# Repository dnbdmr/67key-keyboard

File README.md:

# A mechanical keyboard with a Thinkpad Trackpoint module installed

- Uses a trackpoint module from an old laptop keyboard. Some more details in hw/
- Uses Microchip SAMD21 MCU with TinyUSB
- Shift registers instead of key matrix

[Schematic](media/67keys-trackpoint.pdf)

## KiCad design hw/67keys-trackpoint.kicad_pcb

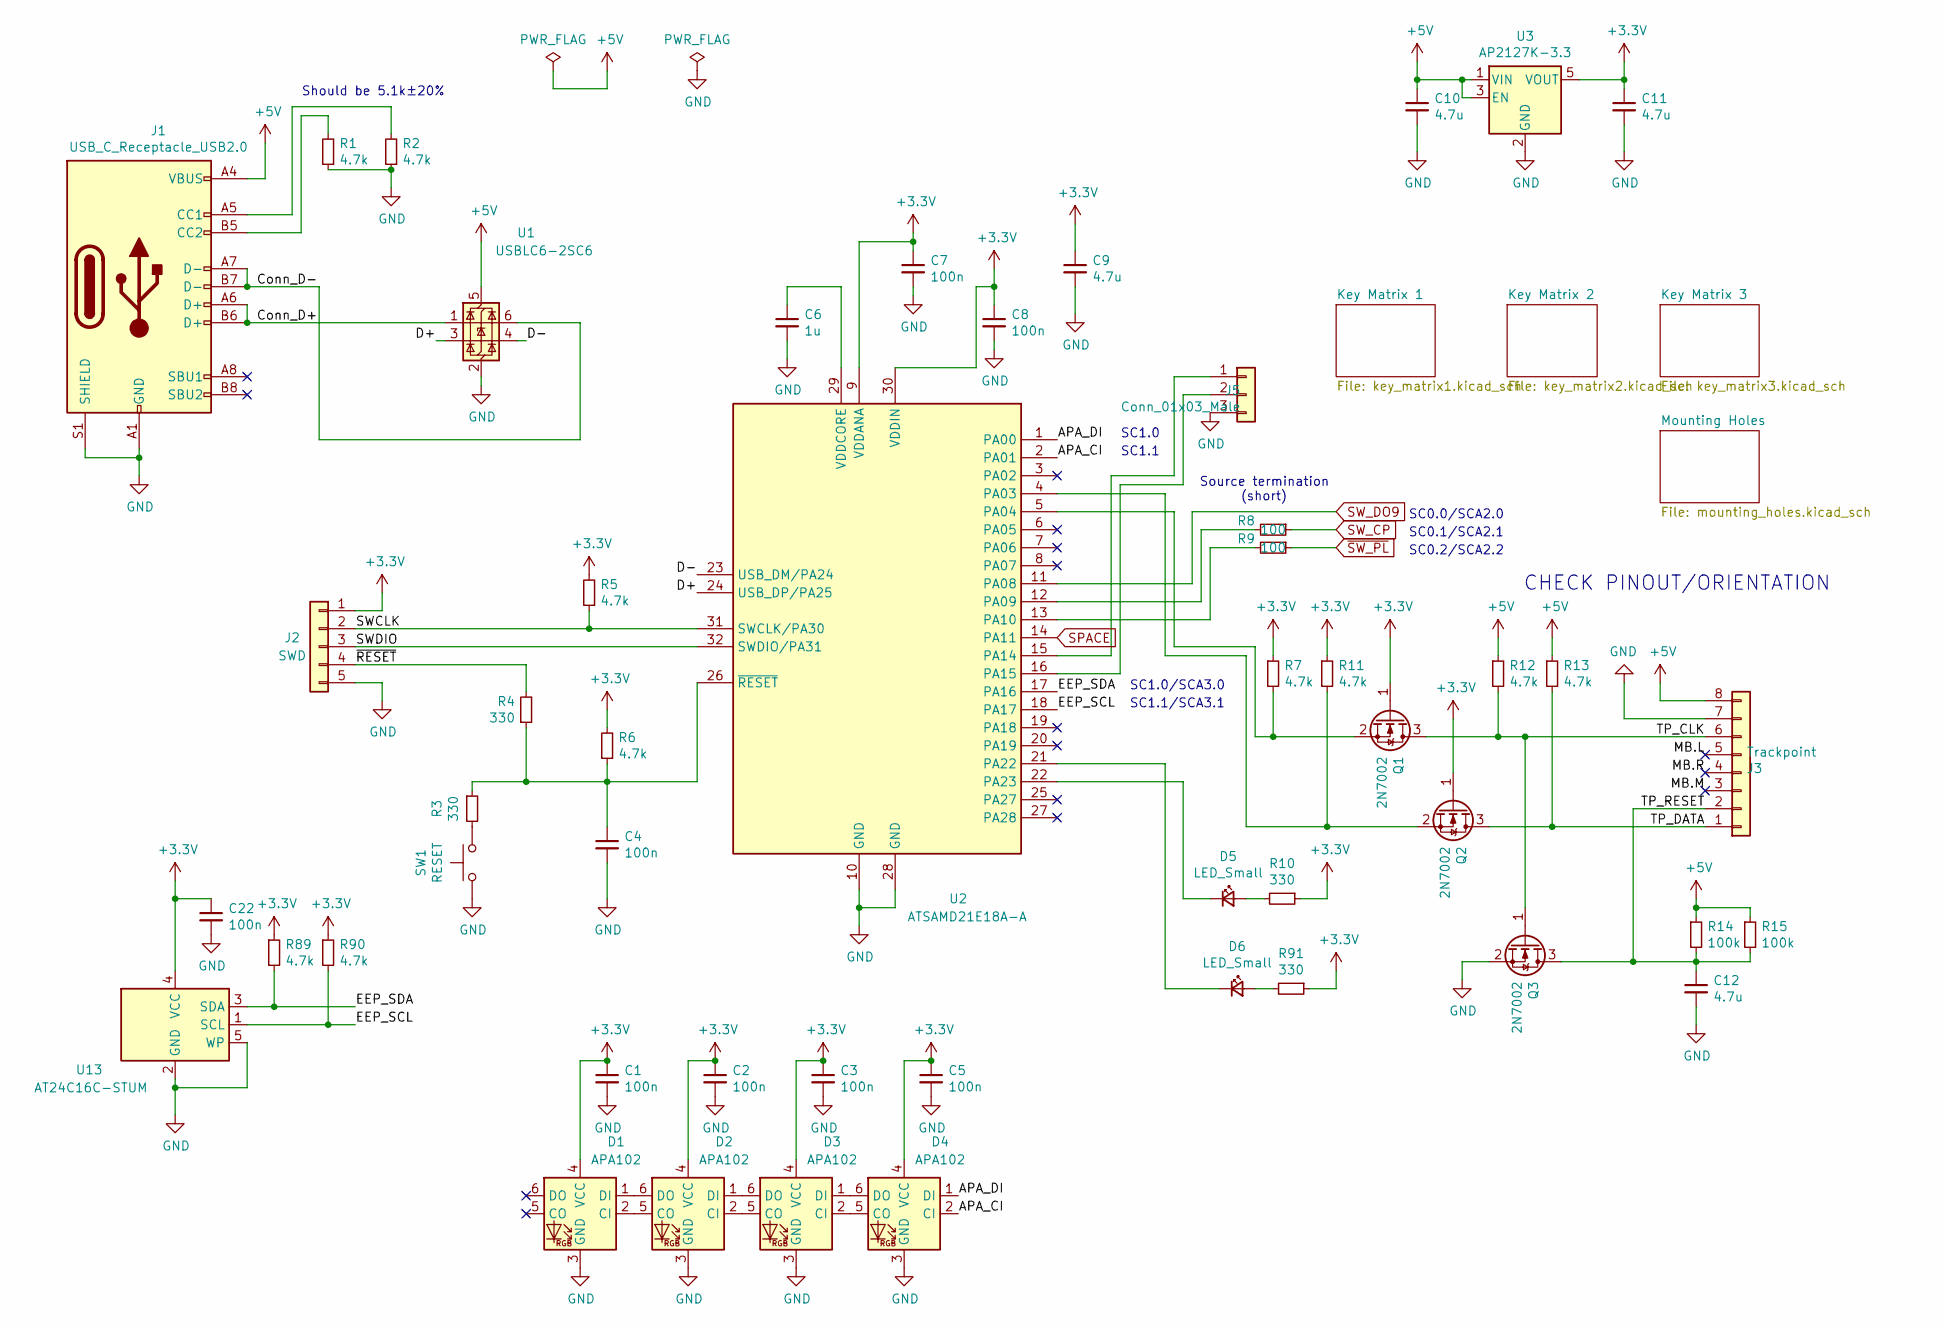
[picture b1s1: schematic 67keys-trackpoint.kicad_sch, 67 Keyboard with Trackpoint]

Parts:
C1, C2, C3, C4, C5, C7, C8, C22: 100n; C_0603_1608Metric_Pad1.08x0.95mm_HandSolder
C6: 1u; C_0603_1608Metric_Pad1.08x0.95mm_HandSolder
C9, C10, C11, C12: 4.7u; C_0603_1608Metric_Pad1.08x0.95mm_HandSolder
D1, D2, D3, D4: APA102; LED_RGB_5050-6
D5, D6: LED_Small; LED_0805_2012Metric_Pad1.15x1.40mm_HandSolder
J1: USB_C_Receptacle_USB2.0; USB_C_Receptacle_GCT_USB4085
J2: SWD; PinHeader_1x05_P2.54mm_Vertical
J3: Trackpoint; TE_84952-8_1x08-1MP_P1.0mm_Horizontal
J5: Conn_01x03_Male; PinHeader_1x03_P2.54mm_Vertical
Q1, Q2, Q3: 2N7002; SOT-23
R1, R2, R5, R6, R7, R11, R12, R13, R89, R90: 4.7k; R_0603_1608Metric_Pad0.98x0.95mm_HandSolder
R3, R4, R10, R91: 330; R_0603_1608Metric_Pad0.98x0.95mm_HandSolder
R8, R9: 100; R_0603_1608Metric_Pad0.98x0.95mm_HandSolder
R14, R15: 100k; R_0603_1608Metric_Pad0.98x0.95mm_HandSolder
SW1: RESET; SW_SPST_TL3305A
U1: USBLC6-2SC6; SOT-23-6
U2: ATSAMD21E18A-A; TQFP-32_7x7mm_P0.8mm
U3: AP2127K-3.3; SOT-23-5
U13: AT24C16C-STUM; SOT-23-5

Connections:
+3V3: C1.1, C2.1, C3.1, C5.1, C7.1, C8.1, C9.1, C11.1, C22.1, D1.4 (VCC), D2.4 (VCC), D3.4 (VCC), D4.4 (VCC), J2.1, Q1.1 (G), Q2.1 (G), R5.2, R6.2, R7.1, R10.1, R11.1, R89.1, R90.1, R91.1, U2.9 (VDDANA), U2.30 (VDDIN), U3.5 (VOUT), U13.4 (VCC); also elsewhere on the board
+5V: C10.1, J1.A4 (VBUS), J1.A9 (VBUS), J1.B4 (VBUS), J1.B9 (VBUS), J3.8, R12.1, R13.1, R14.1, R15.1, U1.5 (VBUS), U3.1 (VIN), U3.3 (EN)
/APA_CI: D4.2 (CI), U2.2 (PA01)
/APA_DI: D4.1 (DI), U2.1 (PA00)
/EEP_SCL: R90.2, U2.18 (PA17), U13.1 (SCL)
/EEP_SDA: R89.2, U2.17 (PA16), U13.3 (SDA)
/SWCLK: J2.2, R5.1, U2.31 (SWCLK/PA30)
/SWDIO: J2.3, U2.32 (SWDIO/PA31)
/TP_CLK: J3.6, Q1.3 (D), Q3.1 (G), R12.2
/TP_DATA: J3.1, Q2.3 (D), R13.2
/TP_RESET: C12.1, J3.2, Q3.3 (D), R14.2, R15.2
/~RESET: J2.4, R4.2
GND: C1.2, C2.2, C3.2, C4.2, C5.2, C6.2, C7.2, C8.2, C9.2, C10.2, C11.2, C12.2, C22.2, D1.3 (GND), D2.3 (GND), D3.3 (GND), D4.3 (GND), J1.A1 (GND), J1.A12 (GND), J1.B1 (GND), J1.B12 (GND), J1.S1 (SHIELD), J2.5, J3.7, J5.3, Q3.2 (S), R1.1, R2.1, SW1.1, U1.2 (GND), U2.10 (GND), U2.28 (GND), U3.2 (GND), U13.2 (GND), U13.5 (WP); also elsewhere on the board
unnamed: C4.1, R3.1, R4.1, R6.1, U2.26 (~RESET)
unnamed: C6.1, U2.29 (VDDCORE)
unnamed: D1.1 (DI), D2.6 (DO)
unnamed: D1.2 (CI), D2.5 (CO)
unnamed: D2.1 (DI), D3.6 (DO)
unnamed: D2.2 (CI), D3.5 (CO)
unnamed: D3.1 (DI), D4.6 (DO)
unnamed: D3.2 (CI), D4.5 (CO)
unnamed: D5.1 (K), U2.22 (PA23)
unnamed: D5.2 (A), R10.2
unnamed: D6.1 (K), U2.21 (PA22)
unnamed: D6.2 (A), R91.2
unnamed: J1.A5 (CC1), R2.2
unnamed: J1.B5 (CC2), R1.2
unnamed: J5.1, U2.15 (PA14)
unnamed: J5.2, U2.16 (PA15)
unnamed: Q1.2 (S), R7.2, U2.5 (PA04)
unnamed: Q2.2 (S), R11.2, U2.4 (PA03)
unnamed: R3.2, SW1.2
unnamed: R8.2, U2.12 (PA09)
unnamed: R9.2, U2.13 (PA10)
SPACE: U2.14 (PA11); also elsewhere on the board
SW_CP: R8.1; also elsewhere on the board
SW_DO9: U2.11 (PA08); also elsewhere on the board
~SW_PL: R9.1; also elsewhere on the board

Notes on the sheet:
SC1.0/SCA3.0
CHECK PINOUT/ORIENTATION
SC1.0
SC1.1
SC0.2/SCA2.2
SC0.0/SCA2.0
SC0.1/SCA2.1
SC1.1/SCA3.1
Should be 5.1k±20%
Source termination (short)

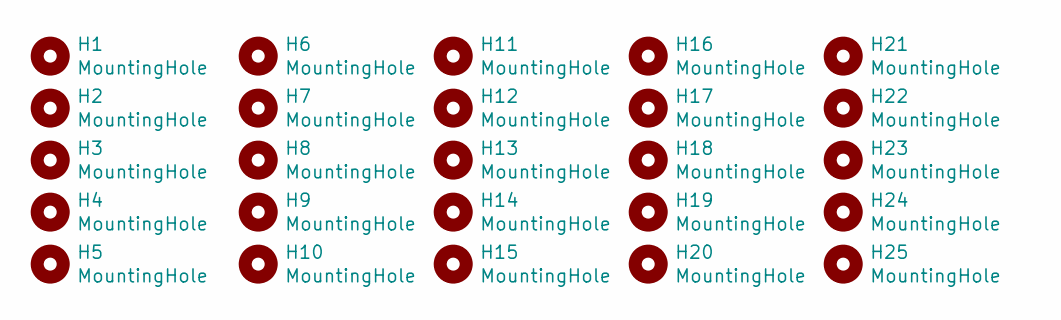
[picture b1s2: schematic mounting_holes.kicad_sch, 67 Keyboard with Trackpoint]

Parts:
H1, H2, H3, H4, H5, H6, H7, H8, H9, H10, H11, H12, H13, H14, H15, H16, H17, H18, H19, H20, H21, H22, H23, H24, H25: MountingHole; MountingHole_2.2mm_M2

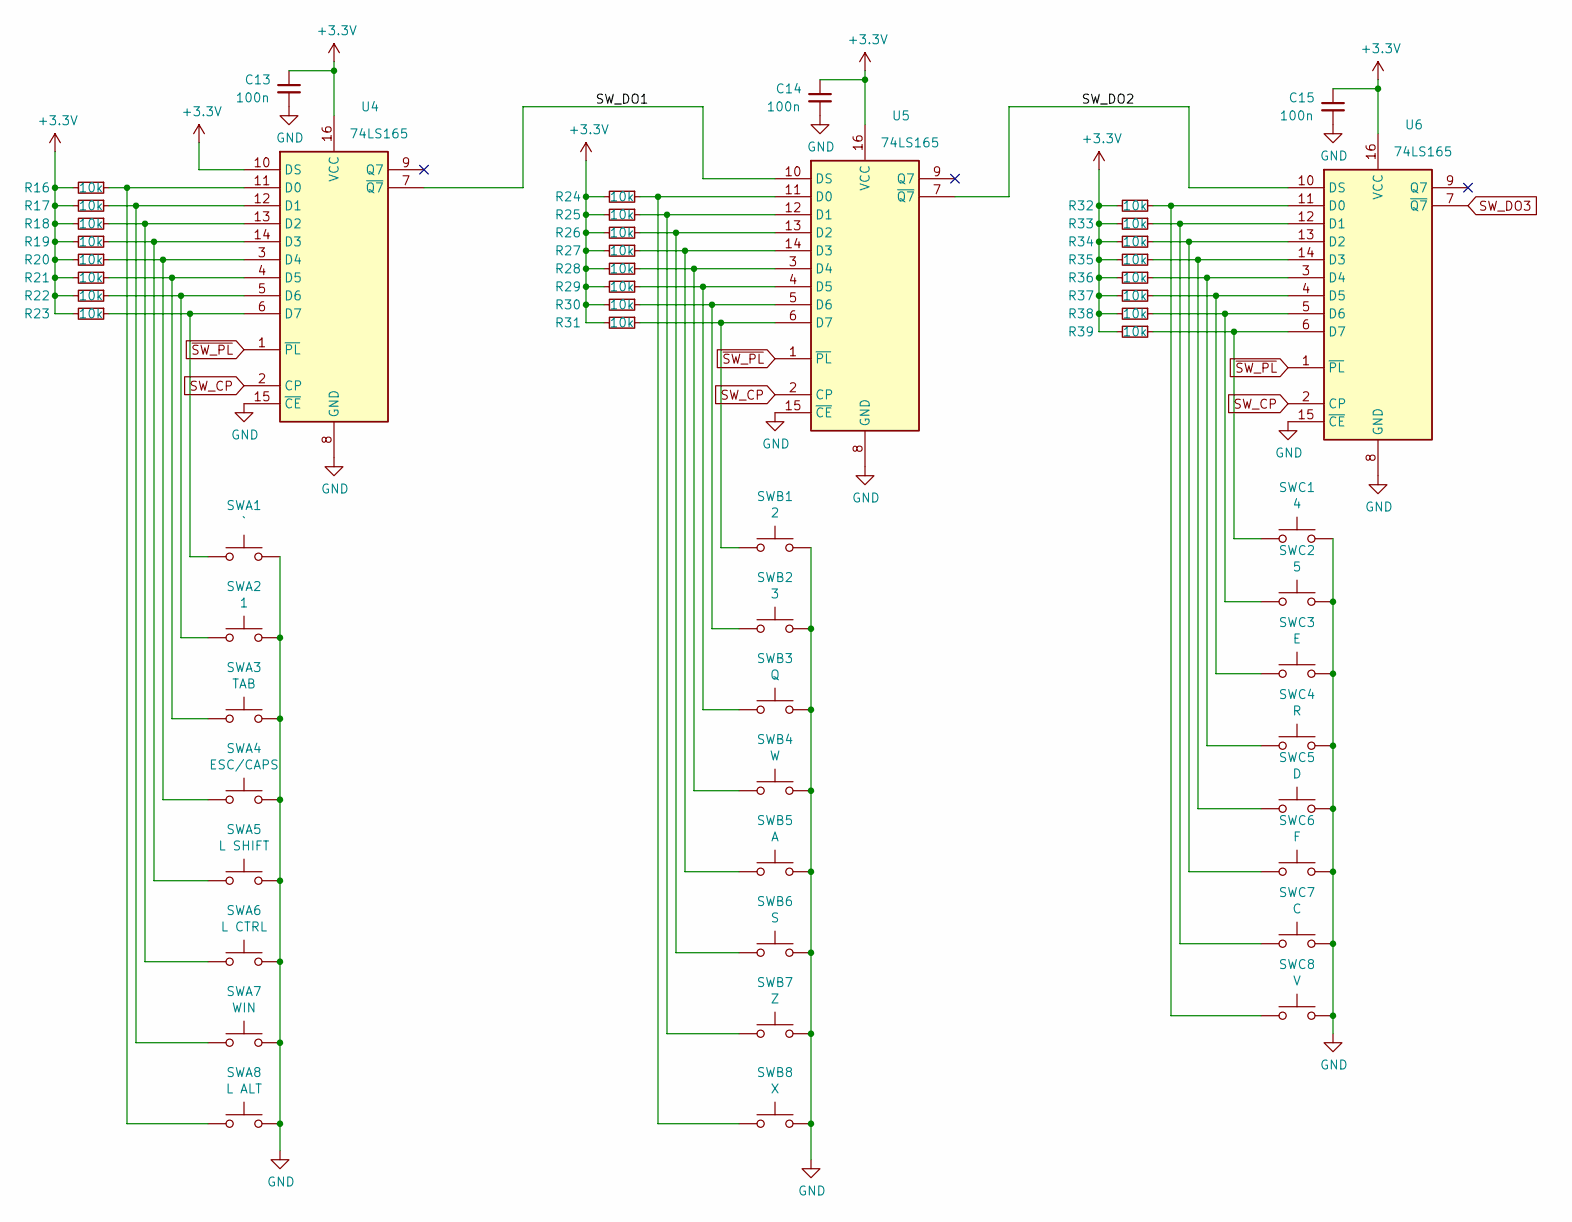
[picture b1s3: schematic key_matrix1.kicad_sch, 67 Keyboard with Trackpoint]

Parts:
C13, C14, C15: 100n; C_0603_1608Metric_Pad1.08x0.95mm_HandSolder
R16, R17, R18, R19, R20, R21, R22, R23, R24, R25, R26, R27, R28, R29, R30, R31, R32, R33, R34, R35, R36, R37, R38, R39: 10k; R_0603_1608Metric_Pad0.98x0.95mm_HandSolder
SWA1: `; SW_Cherry_MX_1.00u_PCB
SWA2: 1; SW_Cherry_MX_1.00u_PCB
SWA3: TAB; SW_Cherry_MX_1.50u_PCB
SWA4: ESC/CAPS; SW_Cherry_MX_1.75u_PCB
SWA5: L SHIFT; SW_Cherry_MX_2.25u_PCB
SWA6: L CTRL; SW_Cherry_MX_1.25u_PCB
SWA7: WIN; SW_Cherry_MX_1.25u_PCB
SWA8: L ALT; SW_Cherry_MX_1.25u_PCB
SWB1: 2; SW_Cherry_MX_1.00u_PCB
SWB2: 3; SW_Cherry_MX_1.00u_PCB
SWB3: Q; SW_Cherry_MX_1.00u_PCB
SWB4: W; SW_Cherry_MX_1.00u_PCB
SWB5: A; SW_Cherry_MX_1.00u_PCB
SWB6: S; SW_Cherry_MX_1.00u_PCB
SWB7: Z; SW_Cherry_MX_1.00u_PCB
SWB8: X; SW_Cherry_MX_1.00u_PCB
SWC1: 4; SW_Cherry_MX_1.00u_PCB
SWC2: 5; SW_Cherry_MX_1.00u_PCB
SWC3: E; SW_Cherry_MX_1.00u_PCB
SWC4: R; SW_Cherry_MX_1.00u_PCB
SWC5: D; SW_Cherry_MX_1.00u_PCB
SWC6: F; SW_Cherry_MX_1.00u_PCB
SWC7: C; SW_Cherry_MX_1.00u_PCB
SWC8: V; SW_Cherry_MX_1.00u_PCB
U4, U5, U6: 74LS165; TSSOP-16_4.4x5mm_P0.65mm

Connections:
+3V3: C13.1, C14.1, C15.1, R16.2, R17.2, R18.2, R19.2, R20.2, R21.2, R22.2, R23.2, R24.2, R25.2, R26.2, R27.2, R28.2, R29.2, R30.2, R31.2, R32.2, R33.2, R34.2, R35.2, R36.2, R37.2, R38.2, R39.2, U4.10 (DS), U4.16 (VCC), U5.16 (VCC), U6.16 (VCC); also elsewhere on the board
/Key Matrix 1/SW_DO1: U4.7 (~Q7), U5.10 (DS)
/Key Matrix 1/SW_DO2: U5.7 (~Q7), U6.10 (DS)
GND: C13.2, C14.2, C15.2, SWA1.2, SWA2.2, SWA3.2, SWA4.2, SWA5.2, SWA6.2, SWA7.2, SWA8.2, SWB1.2, SWB2.2, SWB3.2, SWB4.2, SWB5.2, SWB6.2, SWB7.2, SWB8.2, SWC1.2, SWC2.2, SWC3.2, SWC4.2, SWC5.2, SWC6.2, SWC7.2, SWC8.2, U4.8 (GND), U4.15 (~CE), U5.8 (GND), U5.15 (~CE), U6.8 (GND), U6.15 (~CE); also elsewhere on the board
unnamed: R16.1, SWA8.1, U4.11 (D0)
unnamed: R17.1, SWA7.1, U4.12 (D1)
unnamed: R18.1, SWA6.1, U4.13 (D2)
unnamed: R19.1, SWA5.1, U4.14 (D3)
unnamed: R20.1, SWA4.1, U4.3 (D4)
unnamed: R21.1, SWA3.1, U4.4 (D5)
unnamed: R22.1, SWA2.1, U4.5 (D6)
unnamed: R23.1, SWA1.1, U4.6 (D7)
unnamed: R24.1, SWB8.1, U5.11 (D0)
unnamed: R25.1, SWB7.1, U5.12 (D1)
unnamed: R26.1, SWB6.1, U5.13 (D2)
unnamed: R27.1, SWB5.1, U5.14 (D3)
unnamed: R28.1, SWB4.1, U5.3 (D4)
unnamed: R29.1, SWB3.1, U5.4 (D5)
unnamed: R30.1, SWB2.1, U5.5 (D6)
unnamed: R31.1, SWB1.1, U5.6 (D7)
unnamed: R32.1, SWC8.1, U6.11 (D0)
unnamed: R33.1, SWC7.1, U6.12 (D1)
unnamed: R34.1, SWC6.1, U6.13 (D2)
unnamed: R35.1, SWC5.1, U6.14 (D3)
unnamed: R36.1, SWC4.1, U6.3 (D4)
unnamed: R37.1, SWC3.1, U6.4 (D5)
unnamed: R38.1, SWC2.1, U6.5 (D6)
unnamed: R39.1, SWC1.1, U6.6 (D7)
SW_CP: U4.2 (CP), U5.2 (CP), U6.2 (CP); also elsewhere on the board
SW_DO3: U6.7 (~Q7); also elsewhere on the board
~SW_PL: U4.1 (~PL), U5.1 (~PL), U6.1 (~PL); also elsewhere on the board

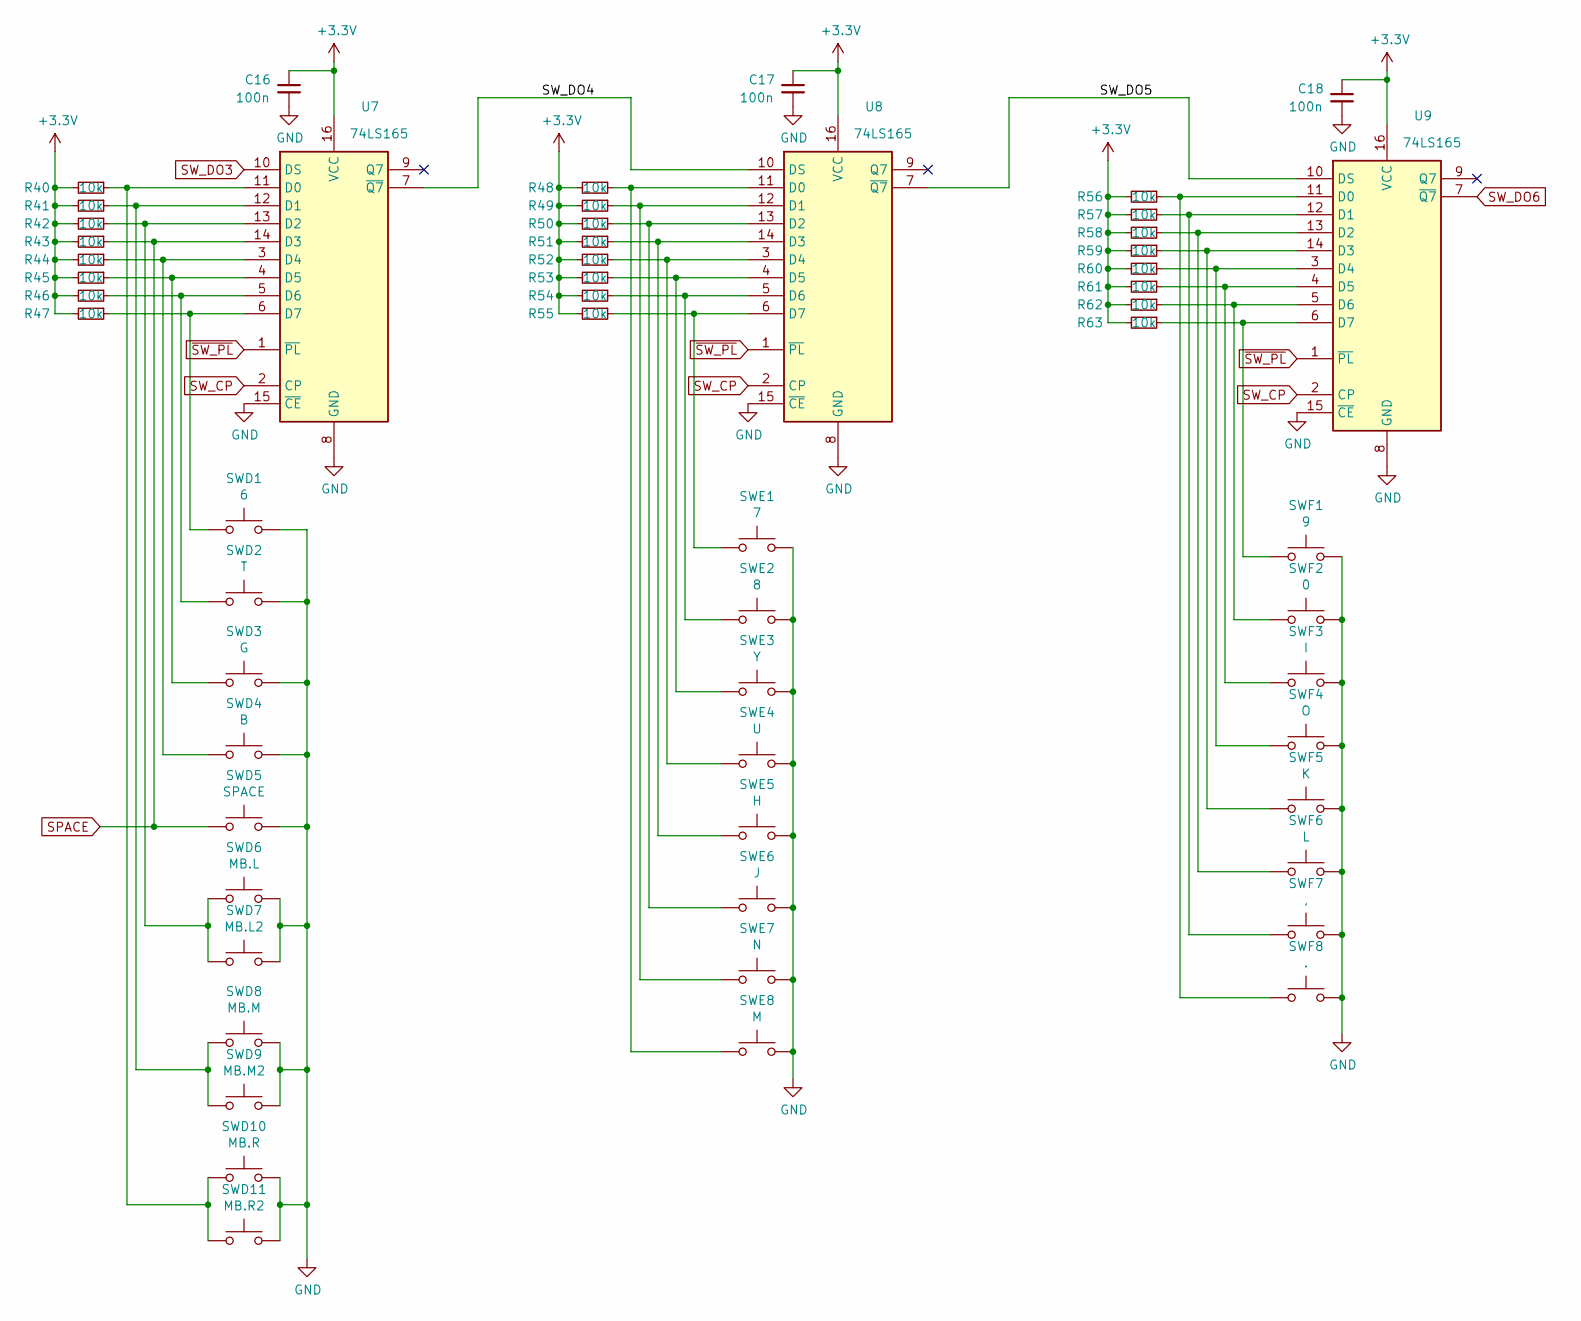
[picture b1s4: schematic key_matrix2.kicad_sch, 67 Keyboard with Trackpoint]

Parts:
C16, C17, C18: 100n; C_0603_1608Metric_Pad1.08x0.95mm_HandSolder
R40, R41, R42, R43, R44, R45, R46, R47, R48, R49, R50, R51, R52, R53, R54, R55, R56, R57, R58, R59, R60, R61, R62, R63: 10k; R_0603_1608Metric_Pad0.98x0.95mm_HandSolder
SWD1: 6; SW_Cherry_MX_1.00u_PCB
SWD2: T; SW_Cherry_MX_1.00u_PCB
SWD3: G; SW_Cherry_MX_1.00u_PCB
SWD4: B; SW_Cherry_MX_1.00u_PCB
SWD5: SPACE; SW_Cherry_MX_6.25u_PCB
SWD6: MB.L; SW_Cherry_MX_1.00u_PCB
SWD7: MB.L2; SW_Tactile_SPST_Angled_PTS645Vx58-2LFS
SWD8: MB.M; SW_Cherry_MX_1.00u_PCB
SWD9: MB.M2; SW_Tactile_SPST_Angled_PTS645Vx58-2LFS
SWD10: MB.R; SW_Cherry_MX_1.00u_PCB
SWD11: MB.R2; SW_Tactile_SPST_Angled_PTS645Vx58-2LFS
SWE1: 7; SW_Cherry_MX_1.00u_PCB
SWE2: 8; SW_Cherry_MX_1.00u_PCB
SWE3: Y; SW_Cherry_MX_1.00u_PCB
SWE4: U; SW_Cherry_MX_1.00u_PCB
SWE5: H; SW_Cherry_MX_1.00u_PCB
SWE6: J; SW_Cherry_MX_1.00u_PCB
SWE7: N; SW_Cherry_MX_1.00u_PCB
SWE8: M; SW_Cherry_MX_1.00u_PCB
SWF1: 9; SW_Cherry_MX_1.00u_PCB
SWF2: 0; SW_Cherry_MX_1.00u_PCB
SWF3: I; SW_Cherry_MX_1.00u_PCB
SWF4: O; SW_Cherry_MX_1.00u_PCB
SWF5: K; SW_Cherry_MX_1.00u_PCB
SWF6: L; SW_Cherry_MX_1.00u_PCB
SWF7: ,; SW_Cherry_MX_1.00u_PCB
SWF8: .; SW_Cherry_MX_1.00u_PCB
U7, U8, U9: 74LS165; TSSOP-16_4.4x5mm_P0.65mm

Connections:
+3V3: C16.1, C17.1, C18.1, R40.2, R41.2, R42.2, R43.2, R44.2, R45.2, R46.2, R47.2, R48.2, R49.2, R50.2, R51.2, R52.2, R53.2, R54.2, R55.2, R56.2, R57.2, R58.2, R59.2, R60.2, R61.2, R62.2, R63.2, U7.16 (VCC), U8.16 (VCC), U9.16 (VCC); also elsewhere on the board
/Key Matrix 2/SW_DO4: U7.7 (~Q7), U8.10 (DS)
/Key Matrix 2/SW_DO5: U8.7 (~Q7), U9.10 (DS)
GND: C16.2, C17.2, C18.2, SWD1.2, SWD2.2, SWD3.2, SWD4.2, SWD5.2, SWD6.2, SWD7.2, SWD8.2, SWD9.2, SWD10.2, SWD11.2, SWE1.2, SWE2.2, SWE3.2, SWE4.2, SWE5.2, SWE6.2, SWE7.2, SWE8.2, SWF1.2, SWF2.2, SWF3.2, SWF4.2, SWF5.2, SWF6.2, SWF7.2, SWF8.2, U7.8 (GND), U7.15 (~CE), U8.8 (GND), U8.15 (~CE), U9.8 (GND), U9.15 (~CE); also elsewhere on the board
unnamed: R40.1, SWD10.1, SWD11.1, U7.11 (D0)
unnamed: R41.1, SWD8.1, SWD9.1, U7.12 (D1)
unnamed: R42.1, SWD6.1, SWD7.1, U7.13 (D2)
unnamed: R44.1, SWD4.1, U7.3 (D4)
unnamed: R45.1, SWD3.1, U7.4 (D5)
unnamed: R46.1, SWD2.1, U7.5 (D6)
unnamed: R47.1, SWD1.1, U7.6 (D7)
unnamed: R48.1, SWE8.1, U8.11 (D0)
unnamed: R49.1, SWE7.1, U8.12 (D1)
unnamed: R50.1, SWE6.1, U8.13 (D2)
unnamed: R51.1, SWE5.1, U8.14 (D3)
unnamed: R52.1, SWE4.1, U8.3 (D4)
unnamed: R53.1, SWE3.1, U8.4 (D5)
unnamed: R54.1, SWE2.1, U8.5 (D6)
unnamed: R55.1, SWE1.1, U8.6 (D7)
unnamed: R56.1, SWF8.1, U9.11 (D0)
unnamed: R57.1, SWF7.1, U9.12 (D1)
unnamed: R58.1, SWF6.1, U9.13 (D2)
unnamed: R59.1, SWF5.1, U9.14 (D3)
unnamed: R60.1, SWF4.1, U9.3 (D4)
unnamed: R61.1, SWF3.1, U9.4 (D5)
unnamed: R62.1, SWF2.1, U9.5 (D6)
unnamed: R63.1, SWF1.1, U9.6 (D7)
SPACE: R43.1, SWD5.1, U7.14 (D3); also elsewhere on the board
SW_CP: U7.2 (CP), U8.2 (CP), U9.2 (CP); also elsewhere on the board
SW_DO3: U7.10 (DS); also elsewhere on the board
SW_DO6: U9.7 (~Q7); also elsewhere on the board
~SW_PL: U7.1 (~PL), U8.1 (~PL), U9.1 (~PL); also elsewhere on the board

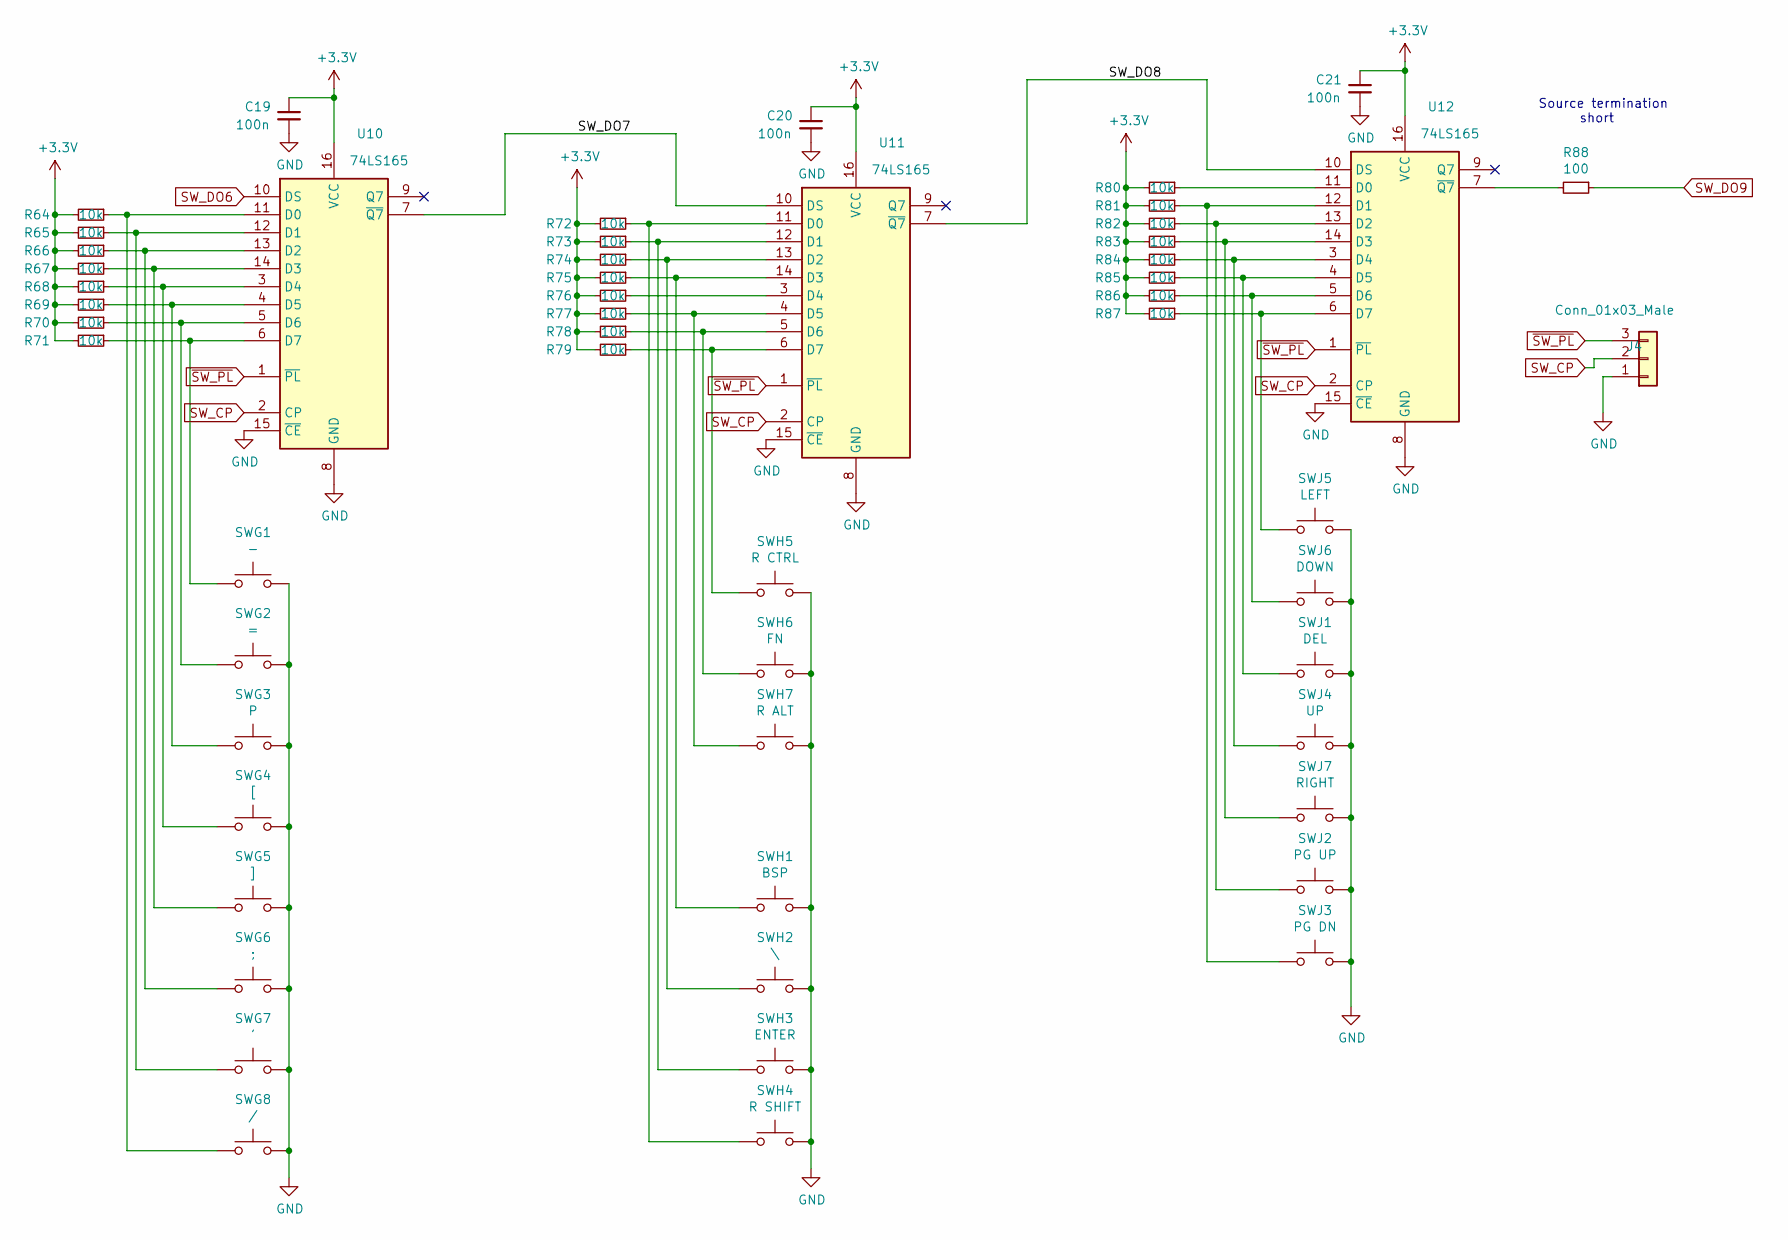
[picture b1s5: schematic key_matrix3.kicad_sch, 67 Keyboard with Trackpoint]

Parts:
C19, C20, C21: 100n; C_0603_1608Metric_Pad1.08x0.95mm_HandSolder
J4: Conn_01x03_Male; PinHeader_1x03_P2.54mm_Vertical
R64, R65, R66, R67, R68, R69, R70, R71, R72, R73, R74, R75, R76, R77, R78, R79, R80, R81, R82, R83, R84, R85, R86, R87: 10k; R_0603_1608Metric_Pad0.98x0.95mm_HandSolder
R88: 100; R_0603_1608Metric_Pad0.98x0.95mm_HandSolder
SWG1: -; SW_Cherry_MX_1.00u_PCB
SWG2: =; SW_Cherry_MX_1.00u_PCB
SWG3: P; SW_Cherry_MX_1.00u_PCB
SWG4: [; SW_Cherry_MX_1.00u_PCB
SWG5: ]; SW_Cherry_MX_1.00u_PCB
SWG6: ;; SW_Cherry_MX_1.00u_PCB
SWG7: '; SW_Cherry_MX_1.00u_PCB
SWG8: /; SW_Cherry_MX_1.00u_PCB
SWH1: BSP; SW_Cherry_MX_2.00u_PCB
SWH2: \; SW_Cherry_MX_1.50u_PCB
SWH3: ENTER; SW_Cherry_MX_2.25u_PCB
SWH4: R SHIFT; SW_Cherry_MX_2.75u_PCB
SWH5: R CTRL; SW_Cherry_MX_1.25u_PCB
SWH6: FN; SW_Cherry_MX_1.25u_PCB
SWH7: R ALT; SW_Cherry_MX_1.25u_PCB
SWJ1: DEL; SW_Cherry_MX_1.00u_PCB
SWJ2: PG UP; SW_Cherry_MX_1.00u_PCB
SWJ3: PG DN; SW_Cherry_MX_1.00u_PCB
SWJ4: UP; SW_Cherry_MX_1.00u_PCB
SWJ5: LEFT; SW_Cherry_MX_1.00u_PCB
SWJ6: DOWN; SW_Cherry_MX_1.00u_PCB
SWJ7: RIGHT; SW_Cherry_MX_1.00u_PCB
U10, U11, U12: 74LS165; TSSOP-16_4.4x5mm_P0.65mm

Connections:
+3V3: C19.1, C20.1, C21.1, R64.2, R65.2, R66.2, R67.2, R68.2, R69.2, R70.2, R71.2, R72.2, R73.2, R74.2, R75.2, R76.2, R77.2, R78.2, R79.2, R80.2, R81.2, R82.2, R83.2, R84.2, R85.2, R86.2, R87.2, U10.16 (VCC), U11.16 (VCC), U12.16 (VCC); also elsewhere on the board
/Key Matrix 3/SW_DO7: U10.7 (~Q7), U11.10 (DS)
/Key Matrix 3/SW_DO8: U11.7 (~Q7), U12.10 (DS)
GND: C19.2, C20.2, C21.2, J4.1, SWG1.2, SWG2.2, SWG3.2, SWG4.2, SWG5.2, SWG6.2, SWG7.2, SWG8.2, SWH1.2, SWH2.2, SWH3.2, SWH4.2, SWH5.2, SWH6.2, SWH7.2, SWJ1.2, SWJ2.2, SWJ3.2, SWJ4.2, SWJ5.2, SWJ6.2, SWJ7.2, U10.8 (GND), U10.15 (~CE), U11.8 (GND), U11.15 (~CE), U12.8 (GND), U12.15 (~CE); also elsewhere on the board
unnamed: R64.1, SWG8.1, U10.11 (D0)
unnamed: R65.1, SWG7.1, U10.12 (D1)
unnamed: R66.1, SWG6.1, U10.13 (D2)
unnamed: R67.1, SWG5.1, U10.14 (D3)
unnamed: R68.1, SWG4.1, U10.3 (D4)
unnamed: R69.1, SWG3.1, U10.4 (D5)
unnamed: R70.1, SWG2.1, U10.5 (D6)
unnamed: R71.1, SWG1.1, U10.6 (D7)
unnamed: R72.1, SWH4.1, U11.11 (D0)
unnamed: R73.1, SWH3.1, U11.12 (D1)
unnamed: R74.1, SWH2.1, U11.13 (D2)
unnamed: R75.1, SWH1.1, U11.14 (D3)
unnamed: R76.1, U11.3 (D4)
unnamed: R77.1, SWH7.1, U11.4 (D5)
unnamed: R78.1, SWH6.1, U11.5 (D6)
unnamed: R79.1, SWH5.1, U11.6 (D7)
unnamed: R80.1, U12.11 (D0)
unnamed: R81.1, SWJ3.1, U12.12 (D1)
unnamed: R82.1, SWJ2.1, U12.13 (D2)
unnamed: R83.1, SWJ7.1, U12.14 (D3)
unnamed: R84.1, SWJ4.1, U12.3 (D4)
unnamed: R85.1, SWJ1.1, U12.4 (D5)
unnamed: R86.1, SWJ6.1, U12.5 (D6)
unnamed: R87.1, SWJ5.1, U12.6 (D7)
unnamed: R88.2, U12.7 (~Q7)
SW_CP: J4.2, U10.2 (CP), U11.2 (CP), U12.2 (CP); also elsewhere on the board
SW_DO6: U10.10 (DS); also elsewhere on the board
SW_DO9: R88.1; also elsewhere on the board
~SW_PL: J4.3, U10.1 (~PL), U11.1 (~PL), U12.1 (~PL); also elsewhere on the board

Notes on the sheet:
Source termination short

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
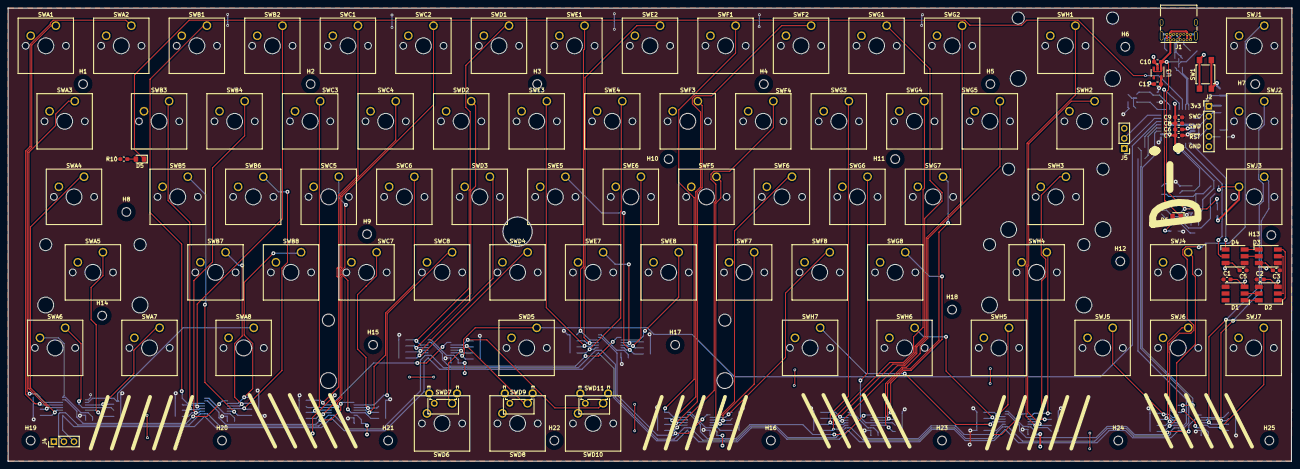
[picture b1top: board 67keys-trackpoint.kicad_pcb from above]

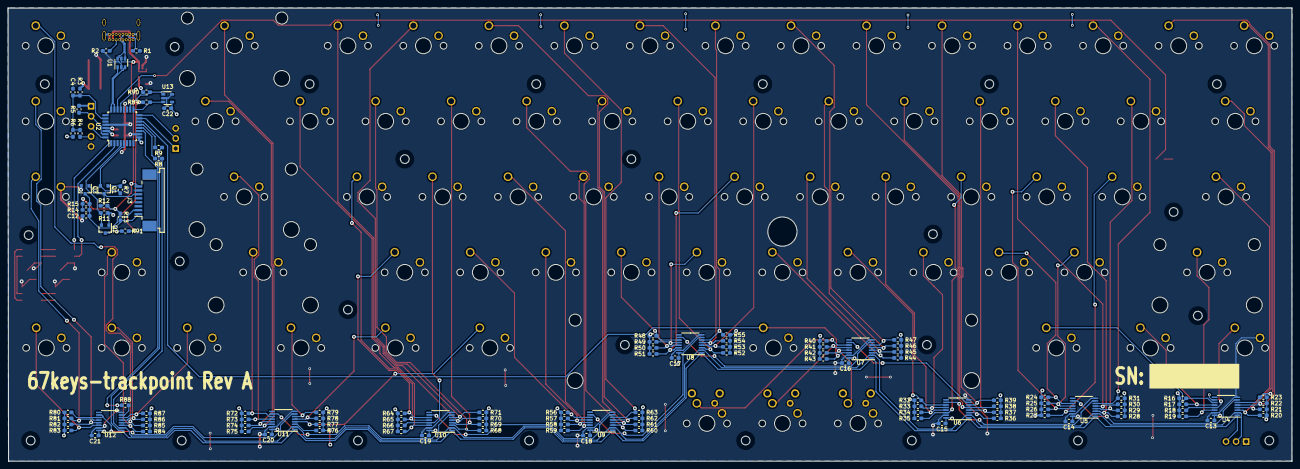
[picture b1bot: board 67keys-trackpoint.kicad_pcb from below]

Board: 2 copper layers, 323.9 x 114.3 mm, 239 parts (118 on the bottom side), 122 nets.

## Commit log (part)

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2020-06-10 Initial commit. Mostly complete.
2020-06-10 Added bypass caps to Dotstars
2020-06-11 Added check note, removed sch-bak from index
2020-06-11 Change symbol for USB connnector
2020-06-12 Run DotStart at 3.3V, add notes
2020-06-12 Completed usb-c
2020-06-12 Annotated, key matrix named after columns/rows
2020-06-12 Assigned footprints
2020-06-12 Layout: board outline, keys, some diodes
2020-06-12 Partial layout
2020-06-13 Almost fully routed, total mess.
    - 10x7 matrix, shuffled around
2020-06-13 Changed to 14x5 matrix, removed LED
2020-06-13 Laid out most diodes. Switched Row 4 and tpclk
2020-06-13 Moved and named APA lines
2020-06-13 Updated some design rules
2020-06-13 Routed. Very ugly.
2020-06-13 Added cuttable jumper to SWD line
2020-06-13 Added notes
2020-06-14 Added tp hole, notes, started footprint
2020-06-14 Added alternat footprints for mouse buttons
2020-06-14 Added some mounting holes
2020-06-14 Moved some references
2020-06-15 Started matrix schematic
2020-06-15 Cleared tracks from pcm
2020-06-15 Split matrix schematic
2020-06-16 Laid out schematic keys
2020-06-17 Finished schematic
    - Laid out shift matrix
    - Added series termination resistors to shift spi
    - Changed label for TP_RESET, should be active high.
2020-06-17 Reannotated pcb keys according to schematic
2020-06-17 Changed sercom texts
2020-06-19 Added eeprom.
2020-06-19 Added mounting holes to schematic
2020-06-19 Started placement
2020-06-19 Started routing, switched TP pins
2020-06-19 Routed, poorly.
2020-06-19 Changed termination resistors to 100 ohm.
2020-06-19 Changed eeprom part number
2020-06-19 Moved references, updated readme
2020-06-20 Renamed local library
2020-06-20 Made trackpoint virtual footprints
2020-06-20 Mount tp module horizontally, moved mounting hole
2020-06-20 Moved some tracks and mounting holes, clearance
2020-06-20 Added extra pin header, some artwork
2020-06-20 Re-added tp footprint
2020-06-20 Added back board design
2020-06-20 Locked keys and mounting holes
2020-06-20 Tied to 3v3 first input to shift regs, U4-10
2020-06-20 Added some artwork, changed a track
2020-06-21 Redid back board
2020-06-21 Adjusted filled areas, moved led trace
2020-06-21 Added direct line to space bar. Stitched some planes
2020-06-21 Tweaked drawings, updated page descriptions
2020-06-21 Tweaked artwork, added SN field
2020-06-22 Clean up tracks
2020-06-22 Shifted usb connector, removed derp
2020-06-23 Removed fp-info-cache
2020-06-23 Made Rev A PCB
2020-06-27 Copied dgw-tiny @ 0e3bbd4
2020-06-27 Added PORT variable to makefile
2020-06-27 Copied some functions from tiny-d11
2020-06-27 Pinned tinyusb to 0.6.0
2020-06-27 Added option to flash with bossa
2020-06-27 CDC readline working
2020-06-27 Added spi, shift reading.
2020-06-29 Split off matrix read
2020-06-29 Remove extra leds
2020-06-29 Enabled HID
    - Copied example code
    - Added report for consumer control usages
2020-06-29 Got hid to do something
2020-07-01 Simple keymap/matrix translation working
2020-07-01 hid_task: remove sleep, allow repeating buttons
2020-07-02 Boots!
2020-07-02 Convert line endings on Makefile, clean up
2020-07-02 Shift SPI working.
2020-07-02 Dotstars working
2020-07-02 Cleaned up matrix read. Started Keymap
2020-07-02 Completed basic keymap, working
2020-07-03 Modifiers working
2020-07-03 Added global config variable
2020-07-03 Mouse keys working
2020-07-03 Trackpoint working, still glitchy
2020-07-04 Added code to set TP sensitivity, buggy
2020-07-04 Changed usb descriptor strings
2020-07-04 Changed HID polling interval to 1ms, task to 5ms
2020-07-04 Clean up
2020-07-04 Edited Readme
2020-07-04 Consumer reports working
2020-07-04 Changed Readme
2020-07-05 force_reset: check for bootloader first
2020-07-05 Changed middle mouse to behave like tp wired kb
2020-07-05 Moved LED stuff out of main, react to SET report
2020-07-05 Set up PWM on LEDs
2020-07-05 Misc changes, reduce TP reset, increase spi speed
2020-07-06 Misc. changes.
    - LED not turning off during sleep
    - speed up led_task, cdc_task
    - reduce hid_task time to 2ms
2020-07-06 Changed todos in Readme
2020-07-08 Fixed LED during sleep. Edit todos, add specs.
2020-07-08 Disable NVM SLEEPPRM per errata
2020-07-09 Wakeup from sleep working with idle(1)
2020-07-09 Edited descriptors, usb now enables remote wakeup
    - Changed HID protocol to keyboard from none. This enables boot boot
    protocol with keyboard.
    - UDEV rule 67key.rules isn't necessary.
2020-07-09 Clean up unused sections and files
2020-07-11 Added gamma array for leds
2020-07-11 Added option to write tp sensitivity value.
    Still need to do a read afterwards.
2020-07-12 Enable EIC sense low level. Still no deepsleep.
2020-07-17 Changes to sleep, updated readme.
2020-07-19 Fixed keymap. Added F keys.
2020-07-26 Added more to layer 1. Modifiers on both layers.
2020-07-27 cdc_task check for proper length, misc cdc changes
2020-07-27 Changed debug printing.
2020-07-29 Updated readme and gitignore
2020-07-31 Deleted unused files.
2020-08-01 Edited todos
2020-08-02 Fixed stalling on tp_data* functions
    - tp\_getDataBit was hanging up on mix between commands and stream mode.
    Set up a timeout in interrupt.
    - Reworked tp\_getDataBit().
    - set sensitivity on start up.
    - changed config structure to initialize at definition.
2020-08-02 Added config struct variable for scroll scaling.
2020-08-05 Added todos
2020-08-06 Added debounce delay, config options
    - One timer for entire matrix
    - Moved polling timer to shift task, added option
    - Added option for debounce timeout
2020-08-07 Eeprom storage working
    - automatically load settings on start up.
    - Haven't set up i2c error checks
    - version control in config
    - left floats in i2c init
2020-08-09 Removed dmb from millis
2020-08-11 Edited readme for last commit.
2020-08-14 Limit scrolling to -1,0,1. Changed default loading.
2020-08-14 Added checks to i2c transactions for config
2020-08-14 Added more config version checks.
2020-08-14 Fixed cdc write busy waiting, debug printing.
2020-08-15 Try to only send report if key is pressed, buggy.
    Need to check if there was a change, not just if something was pressed.
    Sometimes zero reports are necessary.
2020-08-16 Only send hid report if that type is needed, messy.
2020-09-15 Added bootport to makefile
2020-09-15 Tweak scrolllim
2020-09-15 Add to menu reading/writing scrolllim
2020-09-16 Move Fn to rAlt, put rWin in it's place
2021-05-08 Change C89,C90 to 4.7k
2021-05-08 Add disasm recipe to makefile
2021-05-08 Start help menu
2021-05-08 Remove float from i2c_init
2021-05-08 LED brightness
2021-05-08 Readme todos
2021-05-11 Moved to fw/ with git-filter-repo, fixed submodule
2025-11-28 Add trackpoint force Recal
2025-11-28 Clean up hw/, remove plots from index
2025-11-28 Convert to Kicad 9
2025-11-28 Add readme and files
